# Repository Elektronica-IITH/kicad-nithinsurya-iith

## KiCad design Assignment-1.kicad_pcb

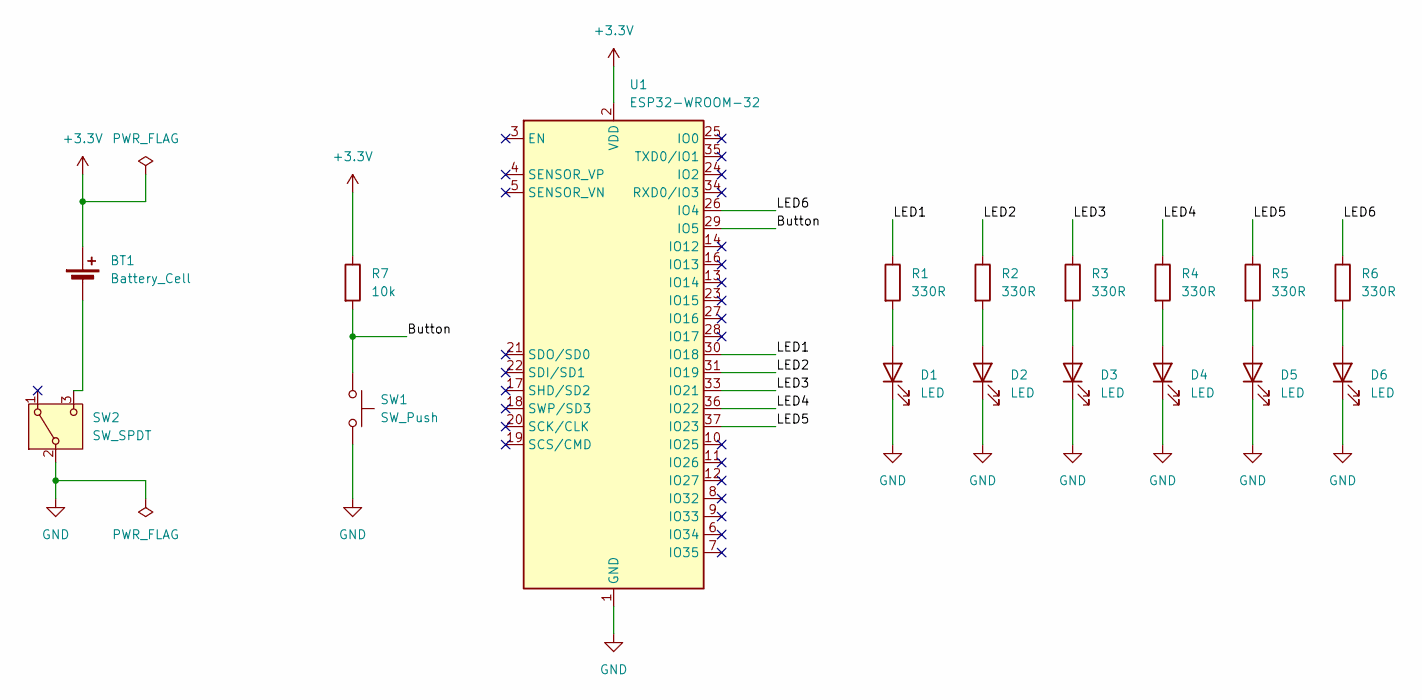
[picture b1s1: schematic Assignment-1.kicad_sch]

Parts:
BT1: Battery_Cell; BatteryHolder_Keystone_104_1x23mm
D1, D2, D3, D4, D5, D6: LED; LED_0201_0603Metric
R1, R2, R3, R4, R5, R6: 330R; R_0201_0603Metric
R7: 10k; R_0201_0603Metric
SW1: SW_Push; SW_PUSH-12mm
SW2: SW_SPDT; SW_SPDT_PCM12
U1: ESP32-WROOM-32

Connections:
+3.3V: BT1.1 (+), R7.1, U1.2 (VDD)
/Button: R7.2, SW1.1, U1.29 (IO5)
/LED1: R1.1, U1.30 (IO18)
/LED2: R2.1, U1.31 (IO19)
/LED3: R3.1, U1.33 (IO21)
/LED4: R4.1, U1.36 (IO22)
/LED5: R5.1, U1.37 (IO23)
/LED6: R6.1, U1.26 (IO4)
GND: D1.1 (K), D2.1 (K), D3.1 (K), D4.1 (K), D5.1 (K), D6.1 (K), SW1.2, SW2.2 (B), U1.1 (GND), U1.15 (GND), U1.38 (GND), U1.39 (GND)
unnamed: BT1.2 (-), SW2.3 (C)
unnamed: D1.2 (A), R1.2
unnamed: D2.2 (A), R2.2
unnamed: D3.2 (A), R3.2
unnamed: D4.2 (A), R4.2
unnamed: D5.2 (A), R5.2
unnamed: D6.2 (A), R6.2

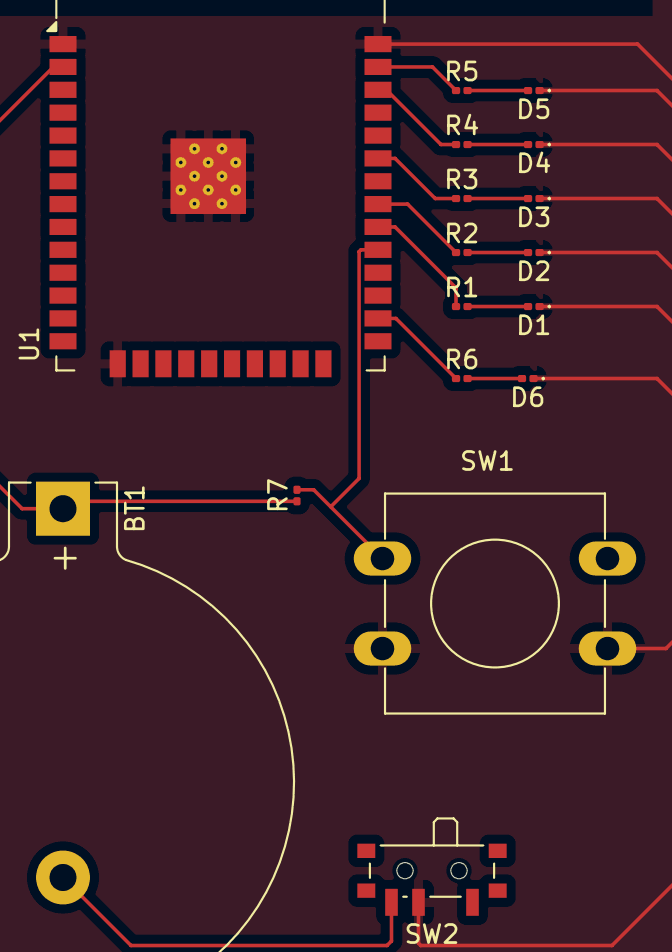
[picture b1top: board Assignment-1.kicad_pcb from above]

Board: 2 copper layers, 17 parts (0 on the bottom side), 16 nets.

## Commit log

2025-03-29 Automated PCB Check: Score 98/100
